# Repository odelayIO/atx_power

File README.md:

# 15 Port USB Power Supply using an ATX Power Supply
<br>
##### View on [gh-page](http://odelayio.github.io/atx_power/)

## Problem Statement
Im continuously using all of my wall outlets to plug-in a USB wall wart power supply to use for all of my development boards (e.g. Raspberry Pi, Arduino, etc).  Over time I needed two 6 port power strips just to have enough outlets for the USB wall wart.  To address this issue, I designed a very simple 15 Power USB power supply using an ATX Power Supply.

## Introduction
This design is a passive USB power supply, meaning this design directly connects the ATX Power Supply +5DCV directly to the +5DCV pin of a USB connector.  I was considering adding a USB charging port controller and current limiting power switch such as the [TSP2511](http://www.ti.com/product/TPS2511).  But I wanted to keep this design simple.

## Parts List
| Name          | Description          | Distrubutor | Price | URL                                                                                                       |
|---------------|----------------------|-------------|-------|-----------------------------------------------------------------------------------------------------------|
| USB Connector | 3 Stack USB          | Mouser      | $4.24 | [Link](http://www.mouser.com/Search/ProductDetail.aspx?R=33UBAR-TSN1Rvirtualkey63110000virtualkey706-33UBAR-TSN1) |
| Binding Post  | For the power supply | Sparkfun    | $0.35 | [Link](https://www.sparkfun.com/products/9739)                                                                    |
| Fuse Holder   | Fuse Clip 5mm        | Sparkfun    | $0.25 | [Link](https://www.sparkfun.com/products/9773)                                                                    |
| PCB           | 15 Port USB          | DirtyPCBs   | $25   | [Link](https://dirtypcbs.com)                                                                                     |

## Assembly

<br>
<br>
######PCB Layout Design
<br>

---
<br>
######I had an old ATX Power Supply, so I just used this one.  This ATX Power Supply cost around $15 on Amazon.com
<br>

---
<br>
######This is the ATX Power Supply with the cover off.  As you can see, there is room in this ATX Power Supply to fit the PCB.
<br>

---
<br>
######This design doesn't use an ATX connect to save money on the BOM. So I trimmed the wires to the desired length.
<br>

---
<br>
######Solder the ATX wires to the designated power rail of the PCB.  The voltage is labeled on the silkscreen.
<br>

---
<br>
######Modified the ATX Power Supply, so the PCB can be mounted
<br>

---
<br>
######Fully assembled 15 Port USB Power Supply.  
<br>

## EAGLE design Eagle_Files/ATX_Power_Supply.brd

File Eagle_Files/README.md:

# Eagle 7.3.0 Design Files

## File Description

- ATX_Power_Supply.sch : Schematic File
- ATX_Power_Supply.brd : Layout File
- ATX_Power_Supply_Gerber274_Final_17NOV2015.zip : Submitted Gerber Files
  - Boards have been fab at http://dirtypcbs.com/

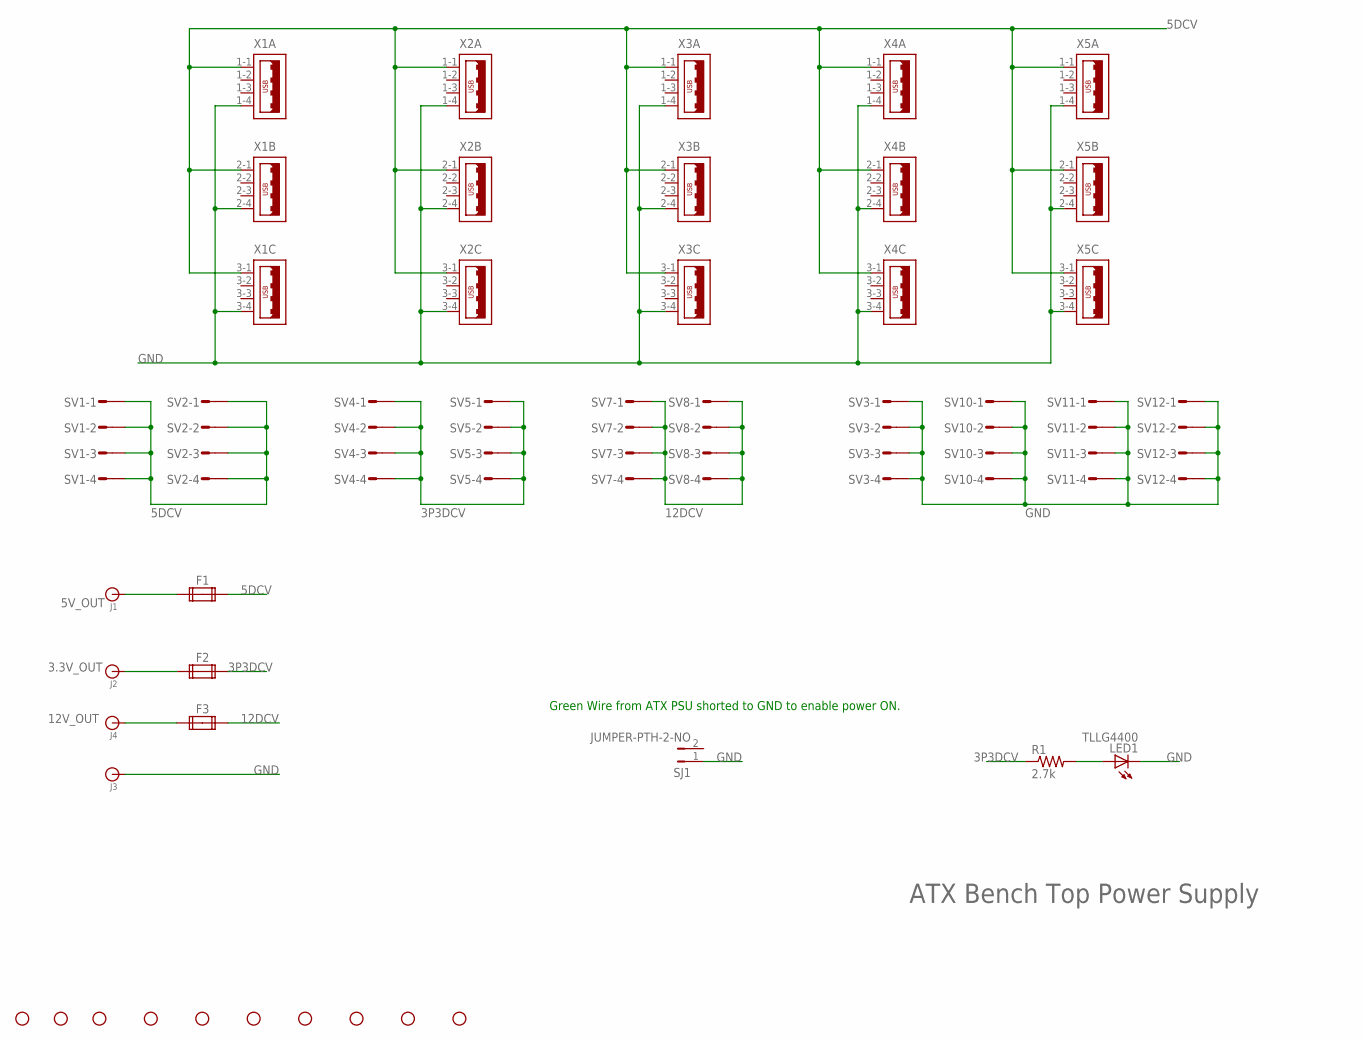
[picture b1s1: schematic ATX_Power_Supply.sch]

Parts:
F1, F2, F3: FUSE2P; FUSE1
J1, J2, J3, J4: BANANA_CONN
LED1: TLLG4400; LED3MM
R1: 2.7k; 0204/5
SJ1: JUMPER-PTH-2-NO; PTH-JUMPER-2-NO_NO_SILK
STANDOFF1, STANDOFF2, STANDOFF3, STANDOFF4, STANDOFF5, STANDOFF6, STANDOFF7, STANDOFF8, STANDOFF9, STANDOFF10: STAND-OFF
SV1, SV2, SV3, SV4, SV5, SV7, SV8, SV10, SV11, SV12: MT6-4
X1, X2, X3, X4, X5: USB_3PSHIELD-85-32003-00X-1; 85-32003-00X-1

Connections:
3.3V_OUT: F2.1A, J2.P$1
3P3DCV: F2.2A, R1.1, SV4.1, SV4.2, SV4.3, SV4.4, SV5.1, SV5.2, SV5.3, SV5.4
5DCV: F1.2A, SV1.1, SV1.2, SV1.3, SV1.4, SV2.1, SV2.2, SV2.3, SV2.4, X1.1-1 (1), X1.2-1 (1), X1.3-1 (1), X2.1-1 (1), X2.2-1 (1), X2.3-1 (1), X3.1-1 (1), X3.2-1 (1), X3.3-1 (1), X4.1-1 (1), X4.2-1 (1), X4.3-1 (1), X5.1-1 (1), X5.2-1 (1), X5.3-1 (1)
5V_OUT: F1.1A, J1.P$1
12DCV: F3.2A, SV7.1, SV7.2, SV7.3, SV7.4, SV8.1, SV8.2, SV8.3, SV8.4
12V_OUT: F3.1A, J4.P$1
GND: J3.P$1, LED1.K (C), SJ1.1, SV3.1, SV3.2, SV3.3, SV3.4, SV10.1, SV10.2, SV10.3, SV10.4, SV11.1, SV11.2, SV11.3, SV11.4, SV12.1, SV12.2, SV12.3, SV12.4, X1.1-4 (4), X1.2-4 (4), X1.3-4 (4), X2.1-4 (4), X2.2-4 (4), X2.3-4 (4), X3.1-4 (4), X3.2-4 (4), X3.3-4 (4), X4.1-4 (4), X4.2-4 (4), X4.3-4 (4), X5.1-4 (4), X5.2-4 (4), X5.3-4 (4)
unnamed: LED1.A, R1.2

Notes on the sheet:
Green Wire from ATX PSU shorted to GND to enable power ON.
ATX Bench Top Power Supply

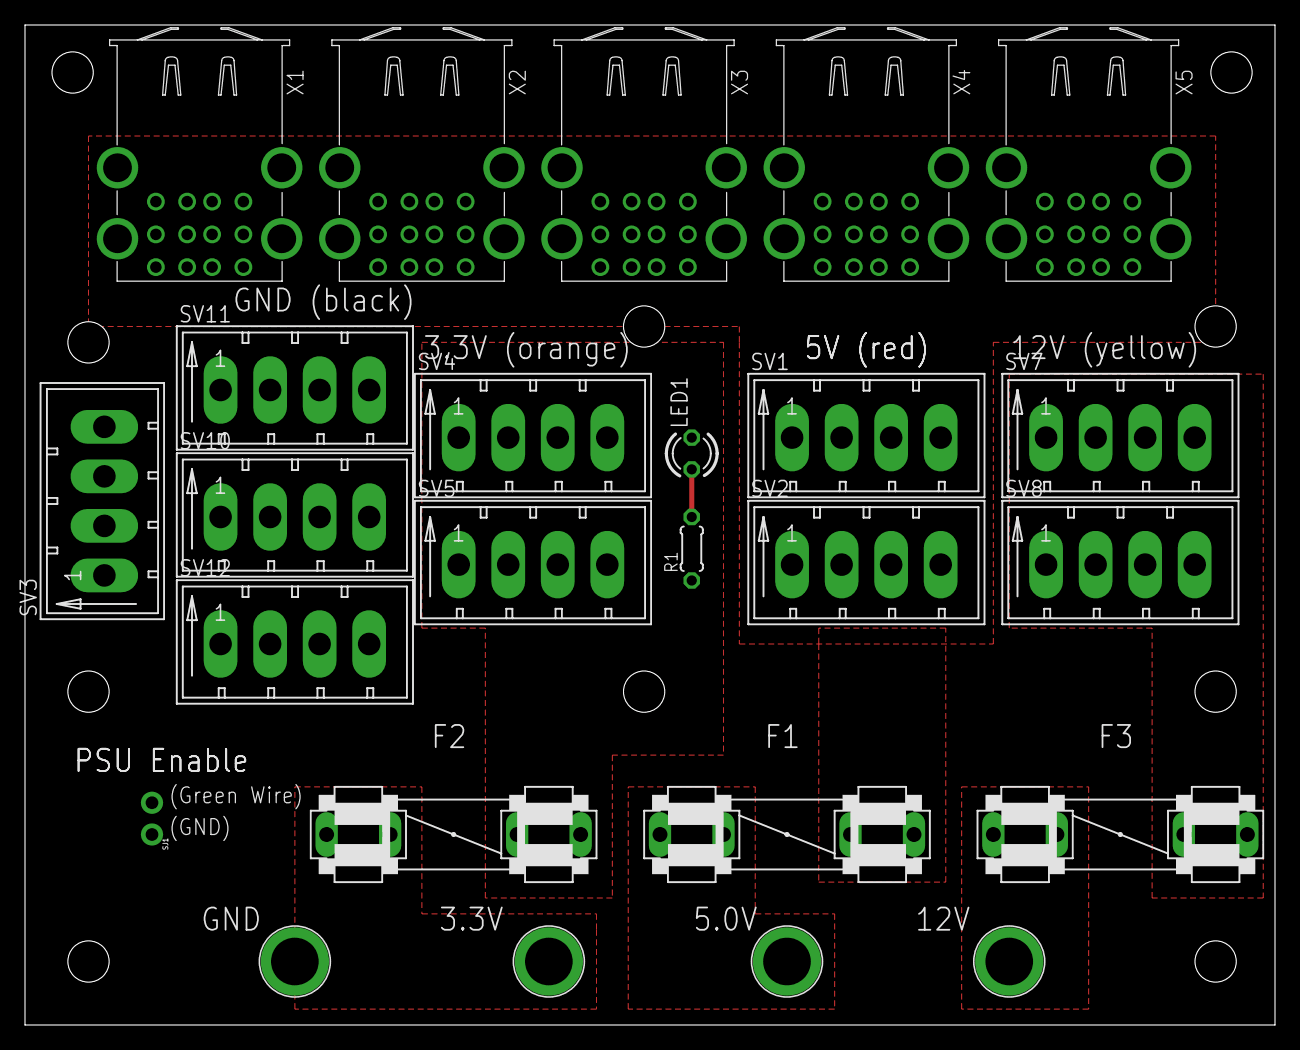
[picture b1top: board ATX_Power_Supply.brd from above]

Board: 2 copper layers, 100.0 x 80.0 mm, 35 parts (0 on the bottom side), 8 nets.

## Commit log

2015-11-26 Create gh-pages branch via GitHub
2016-01-09 update description
2016-01-09 cleaned directory
2016-01-09 Changed Title
2016-01-27 just changed the title
2016-01-27 removed the VI swap file
2016-01-27 Adding Eagle Design Files
2016-01-27 Adding images for USB ATX Power Supply Project
2016-01-27 updated the user name in auto-generated HTML file
2016-01-27 Added description
2016-01-27 added pcb image
2016-01-27 reduced size and added pcb image
2016-01-27 updated image
2016-01-27 alignment change to image
2016-01-27 alignment
2016-01-27 changed formatting
2016-01-28 included gh-pages link

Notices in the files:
parts and their libraries:
SparkFun-Electromechanical: Licensing: Creative Commons ShareAlike 4.0 International - https://creativecommons.org/licenses/by-sa/4.0
